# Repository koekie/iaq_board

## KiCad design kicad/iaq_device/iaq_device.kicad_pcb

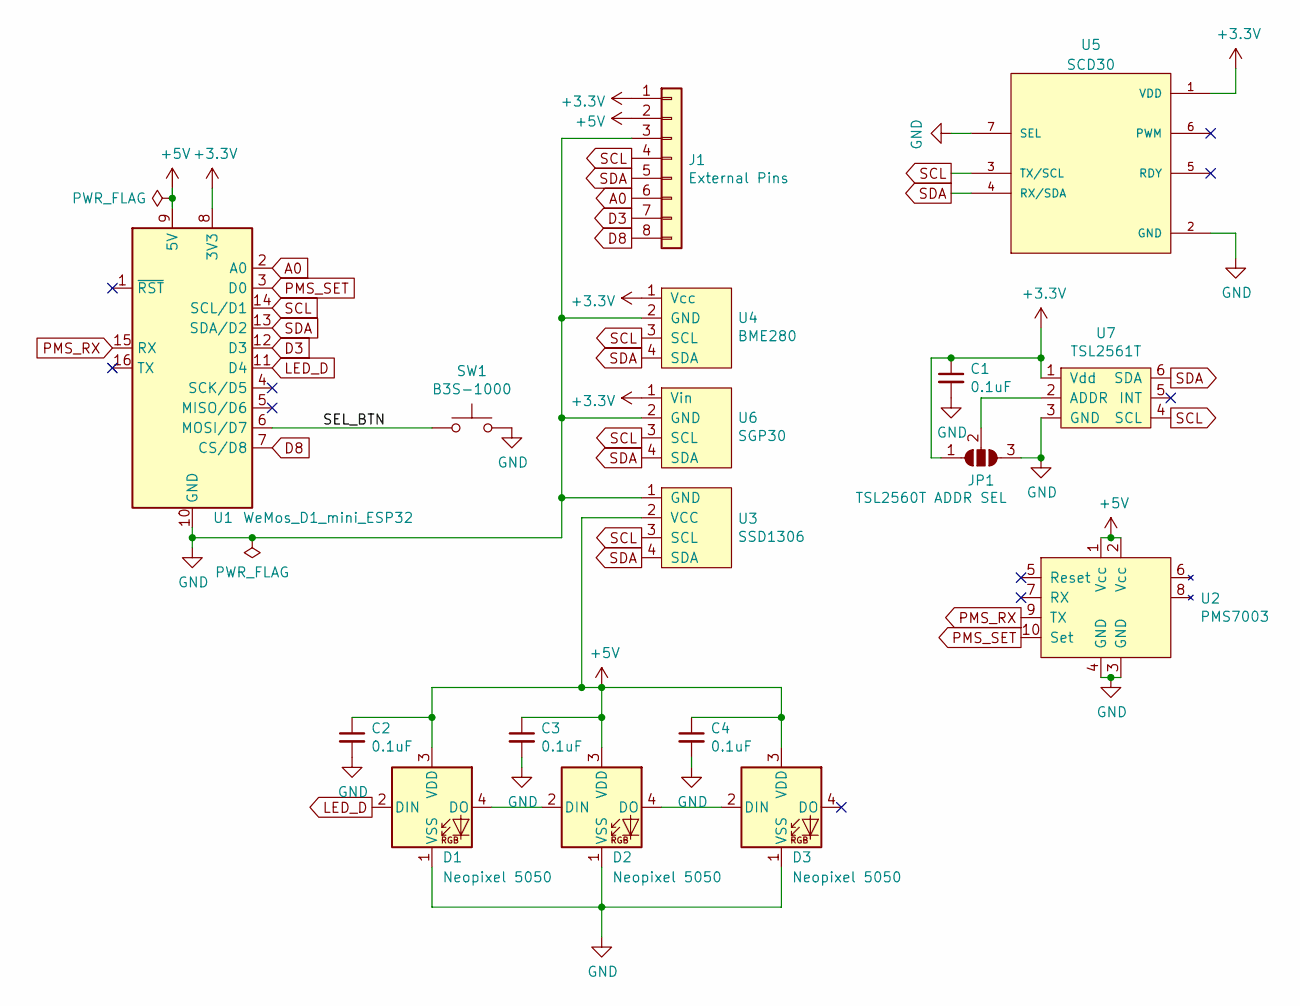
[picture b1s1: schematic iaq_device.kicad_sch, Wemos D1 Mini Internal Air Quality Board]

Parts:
C1, C2, C3, C4: 0.1uF; C_0805_2012Metric
D1, D2, D3: Neopixel 5050; LED_Inolux_IN-PI554FCH_PLCC4_5.0x5.0mm_P3.2mm
J1: External Pins; PinSocket_1x08_P2.54mm_Vertical_SMD_Pin1Left
JP1: TSL2560T ADDR SEL; SolderJumper-3_P1.3mm_Open_RoundedPad1.0x1.5mm_NumberLabels
SW1: B3S-1000; SW_SPST_B3S-1000
U1: WeMos_D1_mini_ESP32; WEMOS_D1_surface
U2: PMS7003
U3: SSD1306
U4: BME280; BME280_breakout_6pin
U5: SCD30; PARTREV D1
U6: SGP30; SGP30_breakout_4pin
U7: TSL2561T

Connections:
+3.3V: C1.1, J1.1, JP1.1 (A), U1.8 (3V3), U4.1 (Vcc), U5.1 (VDD), U6.1 (Vin), U7.1 (Vdd)
+5V: C2.1, C3.1, C4.1, D1.3 (VDD), D2.3 (VDD), D3.3 (VDD), J1.2, U1.9 (5V), U2.1 (Vcc), U2.2 (Vcc), U3.2 (VCC)
/SEL_BTN: SW1.1, U1.6 (MOSI/D7)
A0: J1.6, U1.2 (A0)
D3: J1.7, U1.12 (D3)
D8: J1.8, U1.7 (CS/D8)
GND: C1.2, C2.2, C3.2, C4.2, D1.1 (VSS), D2.1 (VSS), D3.1 (VSS), J1.3, JP1.3 (B), SW1.2, U1.10 (GND), U2.3 (GND), U2.4 (GND), U3.1 (GND), U4.2 (GND), U5.2 (GND), U5.7 (SEL), U6.2 (GND), U7.3 (GND)
LED_D: D1.2 (DIN), U1.11 (D4)
unnamed: D1.4 (DO), D2.2 (DIN)
unnamed: D2.4 (DO), D3.2 (DIN)
unnamed: JP1.2 (C), U7.2 (ADDR)
PMS_RX: U1.15 (RX), U2.9 (TX)
PMS_SET: U1.3 (D0), U2.10 (Set)
SCL: J1.4, U1.14 (SCL/D1), U3.3 (SCL), U4.3 (SCL), U5.3 (TX/SCL), U6.3 (SCL), U7.4 (SCL)
SDA: J1.5, U1.13 (SDA/D2), U3.4 (SDA), U4.4 (SDA), U5.4 (RX/SDA), U6.4 (SDA), U7.6 (SDA)

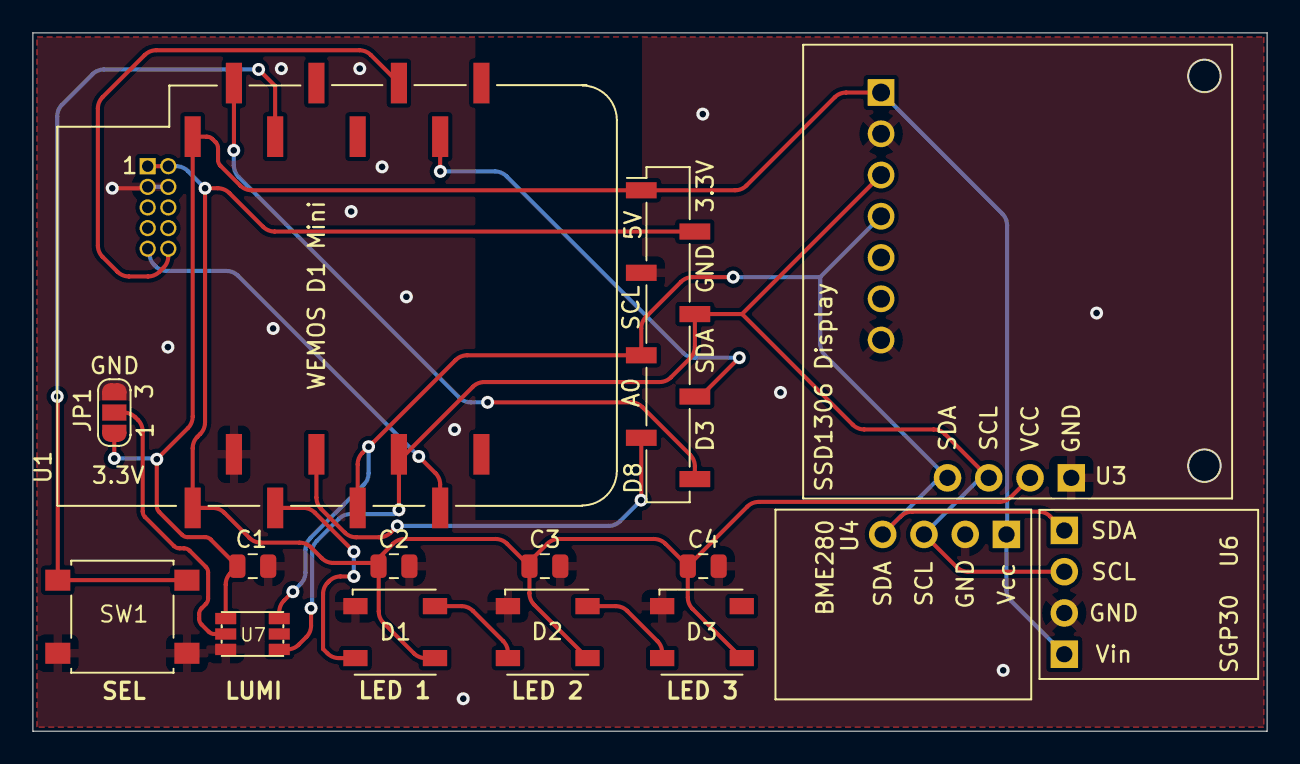
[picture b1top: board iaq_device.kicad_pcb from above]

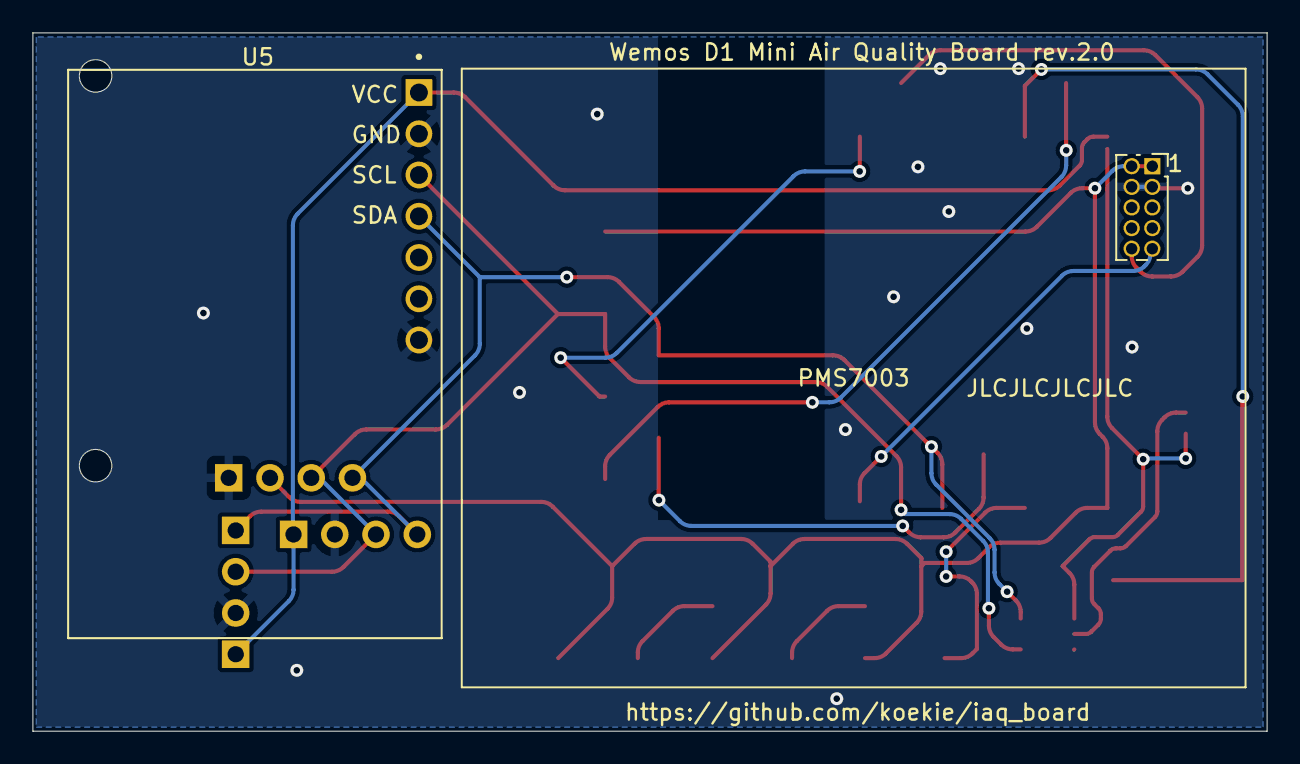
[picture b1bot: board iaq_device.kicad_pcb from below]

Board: 2 copper layers, 76.0 x 43.0 mm, 17 parts (2 on the bottom side), 15 nets.

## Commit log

2023-02-05 fix stuff for kicad and adds scd30 co2 sensor symbol, footprint and 3d model
2023-03-08 lots of changes
2023-03-23 changed co2 sensor to scd30 and rerouted the board
2023-08-28 some small changes to board and updates to kicad 7
2023-08-28 some cleaning
2023-08-28 some housekeeping and cleaning
2023-08-28 updates the firmware readme
